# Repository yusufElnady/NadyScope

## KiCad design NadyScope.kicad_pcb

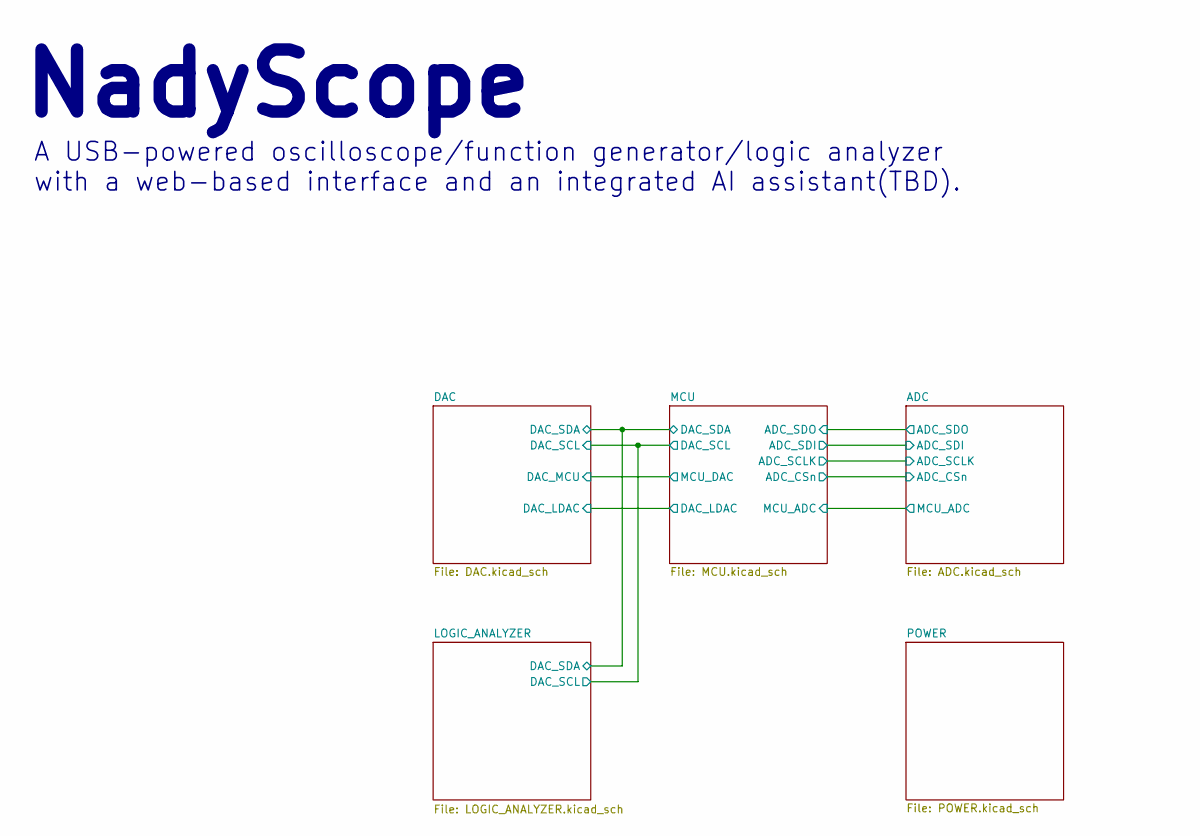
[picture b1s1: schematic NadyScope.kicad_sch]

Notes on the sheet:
A USB-powered oscilloscope/function generator/logic analyzer with a web-based interface and an integrated AI assistant(TBD).
NadyScope

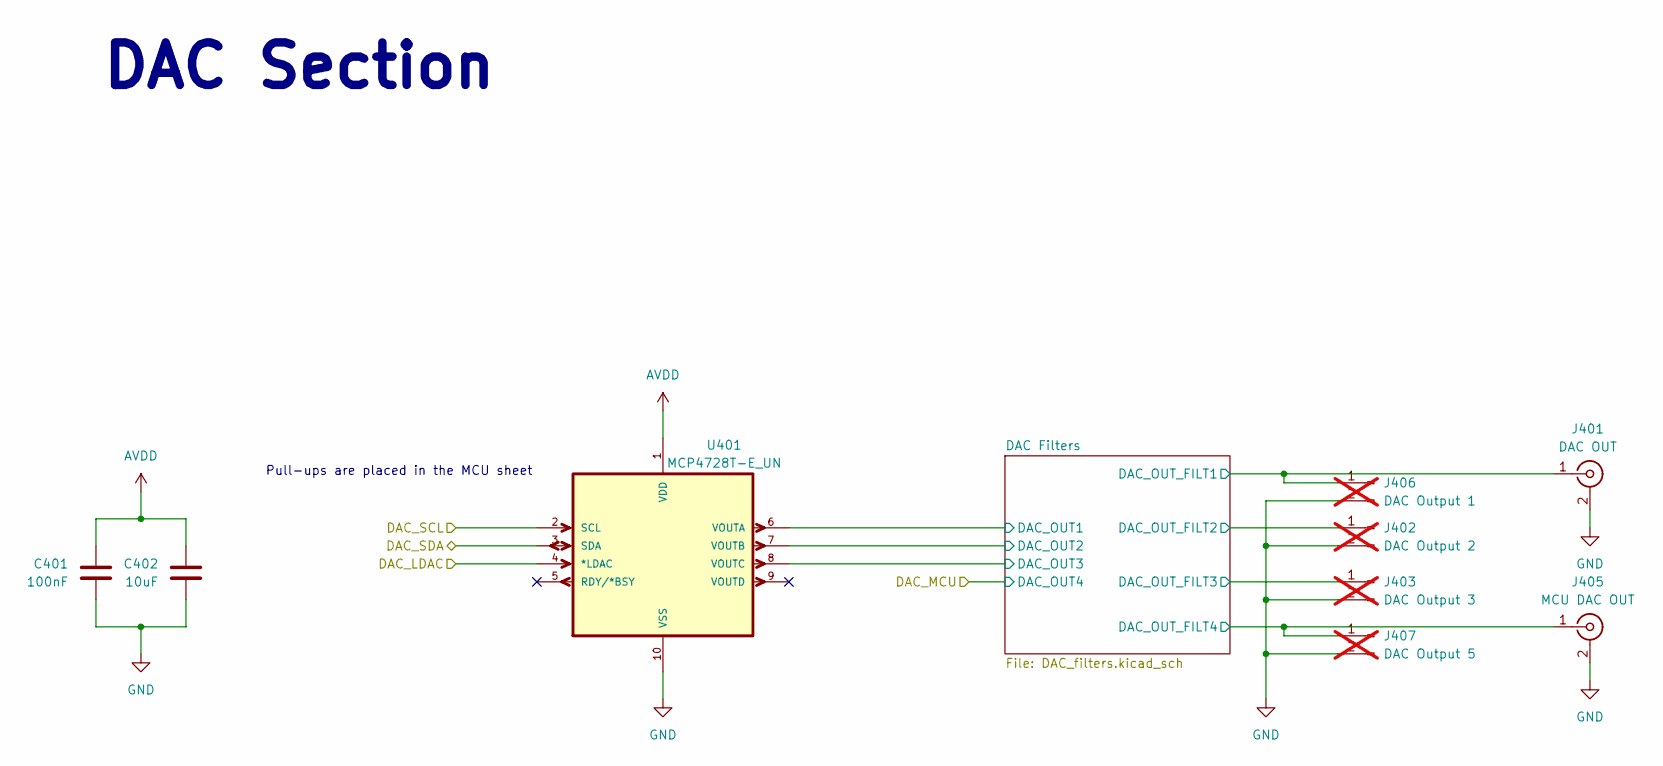
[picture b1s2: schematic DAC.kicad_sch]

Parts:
C401: 100nF; C_0603_1608Metric; MPN 0603B104M250CT
C402: 10uF; C_0603_1608Metric; MPN CL10A106MP8NNNC
J401: DAC OUT; CONN4_DOSIN-801_DOS; MPN DOSIN-801-0083
J402: DAC Output 2; PinHeader_1x02_P2.54mm_Vertical; not fitted
J403: DAC Output 3; PinHeader_1x02_P2.54mm_Vertical; not fitted
J405: MCU DAC OUT; CONN4_DOSIN-801_DOS; MPN DOSIN-801-0083
J406: DAC Output 1; PinHeader_1x02_P2.54mm_Vertical; not fitted
J407: DAC Output 5; PinHeader_1x02_P2.54mm_Vertical; not fitted
U401: MCP4728T-E_UN; SOP50P490X110-10N; MPN MCP4728T-E/UN

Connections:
/DAC/DAC Filters/DAC_OUT1: U401.6 (VOUTA); also elsewhere on the board
/DAC/DAC Filters/DAC_OUT2: U401.7 (VOUTB); also elsewhere on the board
/DAC/DAC Filters/DAC_OUT3: U401.8 (VOUTC); also elsewhere on the board
/DAC/DAC Filters/DAC_OUT_FILT1: J401.1 (In), J406.1; also elsewhere on the board
/DAC/DAC Filters/DAC_OUT_FILT2: J402.1; also elsewhere on the board
/DAC/DAC Filters/DAC_OUT_FILT3: J403.1; also elsewhere on the board
/DAC/DAC Filters/DAC_OUT_FILT4: J405.1 (In), J407.1; also elsewhere on the board
/DAC/DAC_LDAC: U401.4 (*LDAC); also elsewhere on the board
/DAC/DAC_SCL: U401.2 (SCL); also elsewhere on the board
/DAC/DAC_SDA: U401.3 (SDA); also elsewhere on the board
AVDD: C401.1, C402.1, U401.1 (VDD); also elsewhere on the board
GND: C401.2, C402.2, J401.2 (Ext), J402.2, J403.2, J405.2 (Ext), J406.2, J407.2, U401.10 (VSS); also elsewhere on the board

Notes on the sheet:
DAC Section
Pull-ups are placed in the MCU sheet

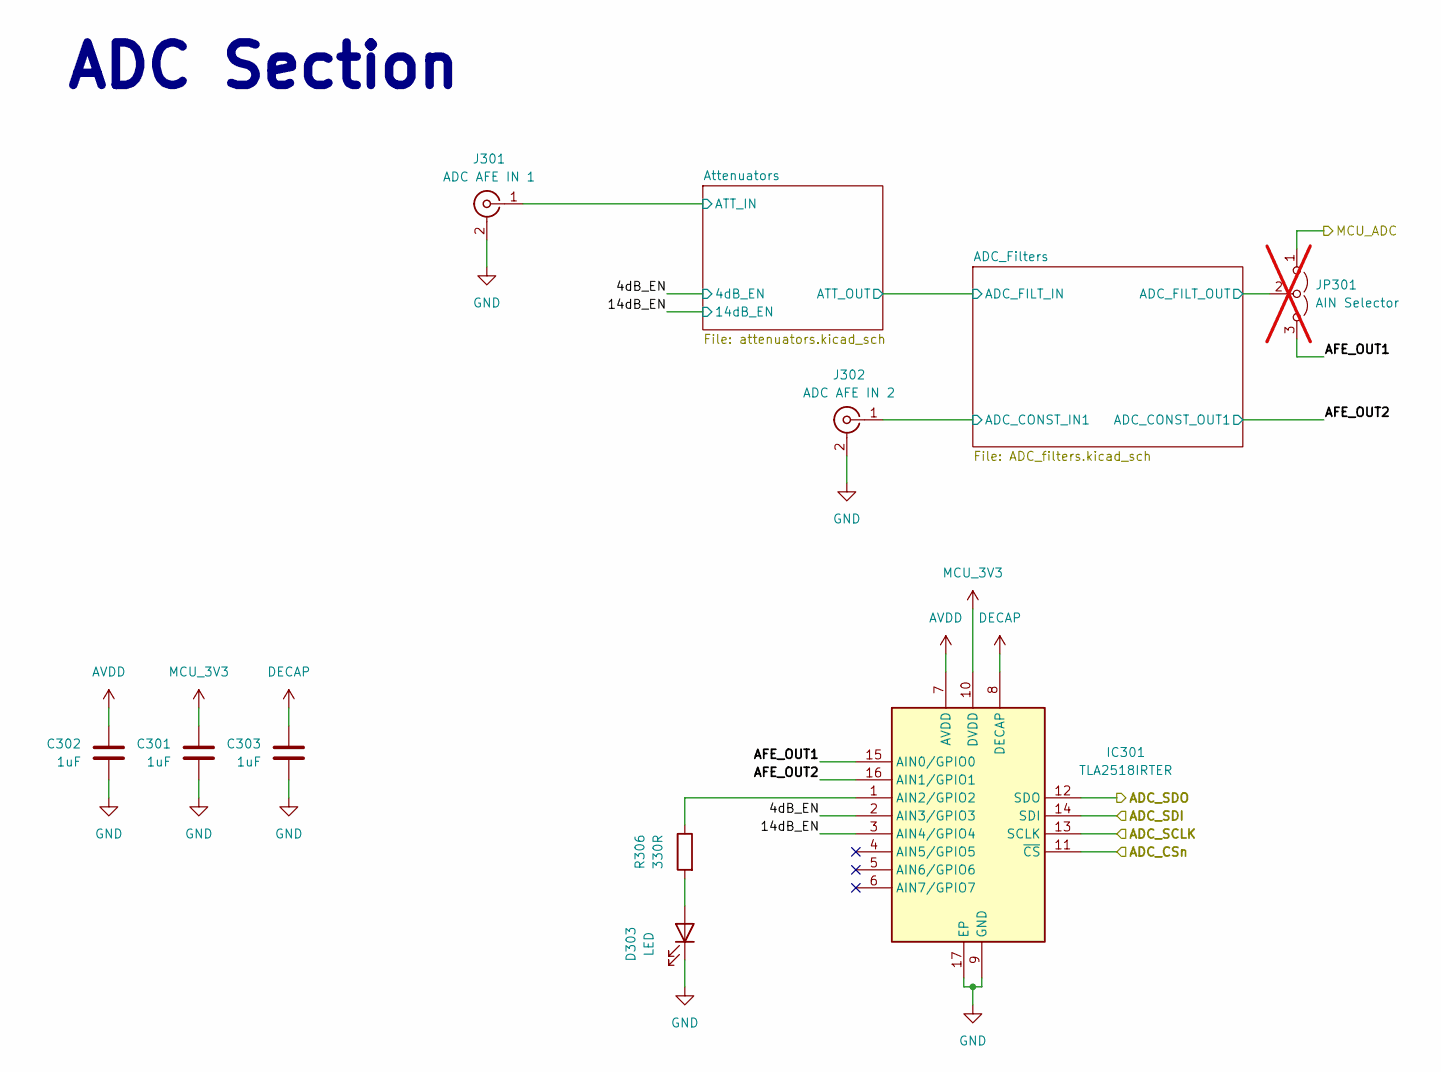
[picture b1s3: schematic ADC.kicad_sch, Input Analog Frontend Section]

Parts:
C301, C302, C303: 1uF; C_0603_1608Metric; MPN 0603X105K250CT
D303: LED; LED_0805_2012Metric
IC301: TLA2518IRTER; QFN50P300X300X80-17N-D; Manufacturer_Part_Number TLA2518IRTER; Mouser Part Number 595-TLA2518IRTER
J301: ADC AFE IN 1; CONN4_DOSIN-801_DOS; MPN DOSIN-801-0083
J302: ADC AFE IN 2; CONN4_DOSIN-801_DOS; MPN DOSIN-801-0083
JP301: AIN Selector; SolderJumper-3_P1.3mm_Open_Pad1.0x1.5mm; not fitted
R306: 330R; R_0603_1608Metric; MPN TD03G3300BT

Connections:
/ADC/4dB_EN: IC301.2 (AIN3/GPIO3); also elsewhere on the board
/ADC/14dB_EN: IC301.3 (AIN4/GPIO4); also elsewhere on the board
/ADC/ADC_CSn: IC301.11 (~CS); also elsewhere on the board
/ADC/ADC_Filters/ADC_FILT_OUT: JP301.2 (C); also elsewhere on the board
/ADC/ADC_SCLK: IC301.13 (SCLK); also elsewhere on the board
/ADC/ADC_SDI: IC301.14 (SDI); also elsewhere on the board
/ADC/ADC_SDO: IC301.12 (SDO); also elsewhere on the board
/ADC/AFE_OUT1: IC301.15 (AIN0/GPIO0), JP301.3 (B)
/ADC/AFE_OUT2: IC301.16 (AIN1/GPIO1); also elsewhere on the board
/ADC/MCU_ADC: JP301.1 (A); also elsewhere on the board
AVDD: C302.1, IC301.7 (AVDD); also elsewhere on the board
DECAP: C303.1, IC301.8 (DECAP)
GND: C301.2, C302.2, C303.2, D303.1 (K), IC301.9 (GND), IC301.17 (EP), J301.2 (Ext), J302.2 (Ext); also elsewhere on the board
MCU_3V3: C301.1, IC301.10 (DVDD); also elsewhere on the board
unnamed: D303.2 (A), R306.2
unnamed: IC301.1 (AIN2/GPIO2), R306.1

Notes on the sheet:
ADC Section

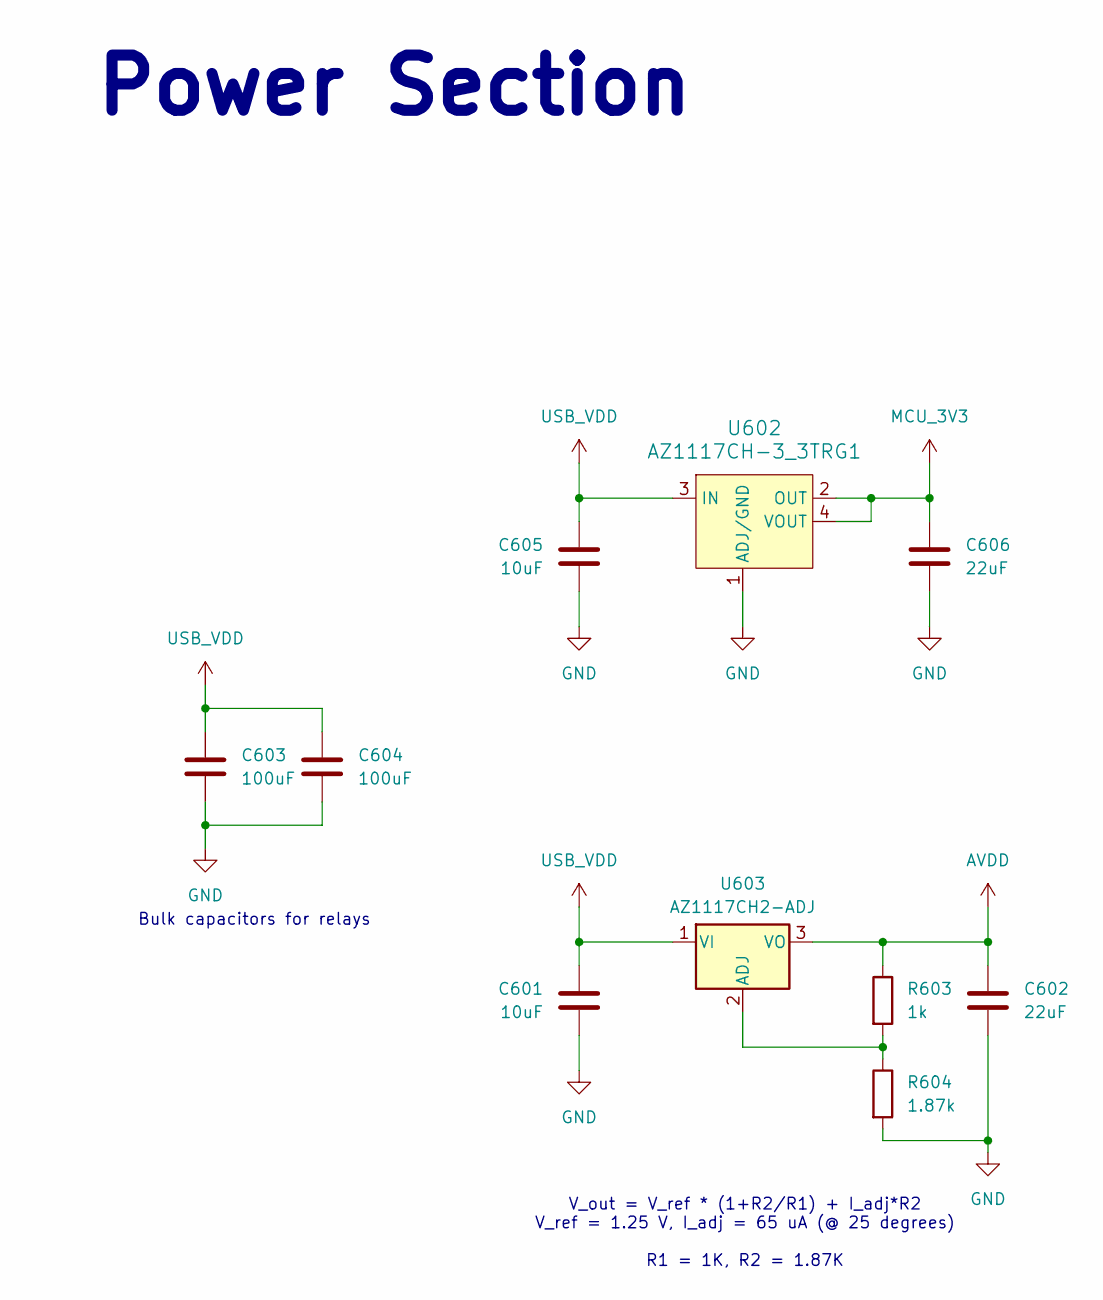
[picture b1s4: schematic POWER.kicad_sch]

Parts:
C601, C605: 10uF; C_0805_2012Metric; MPN CL21A106KOQNNNE
C602, C606: 22uF; C_0805_2012Metric; MPN CL21X226MRQNNNE
C603, C604: 100uF; C_1206_3216Metric; MPN TCC1206X7R103M501DTS
R603: 1k; R_0603_1608Metric; MPN RT0603BRD071KL
R604: 1.87k; R_0603_1608Metric; MPN PTFR0603B1K87N9
U602: AZ1117CH-3_3TRG1; SOT-223; MPN AZ1117CH-3.3TRG1; Digi-Key_PN AZ1117CH-3.3TRG1DICT-ND
U603: AZ1117CH2-ADJ; SOT-223-3_TabPin2; MPN AZ1117CH2-ADJ

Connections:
AVDD: C602.1, R603.1, U603.3 (VO); also elsewhere on the board
GND: C601.2, C602.2, C603.2, C604.2, C605.2, C606.2, R604.2, U602.1 (ADJ/GND); also elsewhere on the board
MCU_3V3: C606.1, U602.2 (OUT), U602.4 (VOUT); also elsewhere on the board
unnamed: R603.2, R604.1, U603.2 (ADJ)
USB_VDD: C601.1, C603.1, C604.1, C605.1, U602.3 (IN), U603.1 (VI); also elsewhere on the board

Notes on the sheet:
Bulk capacitors for relays
V_out = V_ref * (1+R2/R1) + I_adj*R2 V_ref = 1.25 V, I_adj = 65 uA (@ 25 degrees) R1 = 1K, R2 = 1.87K
Power Section

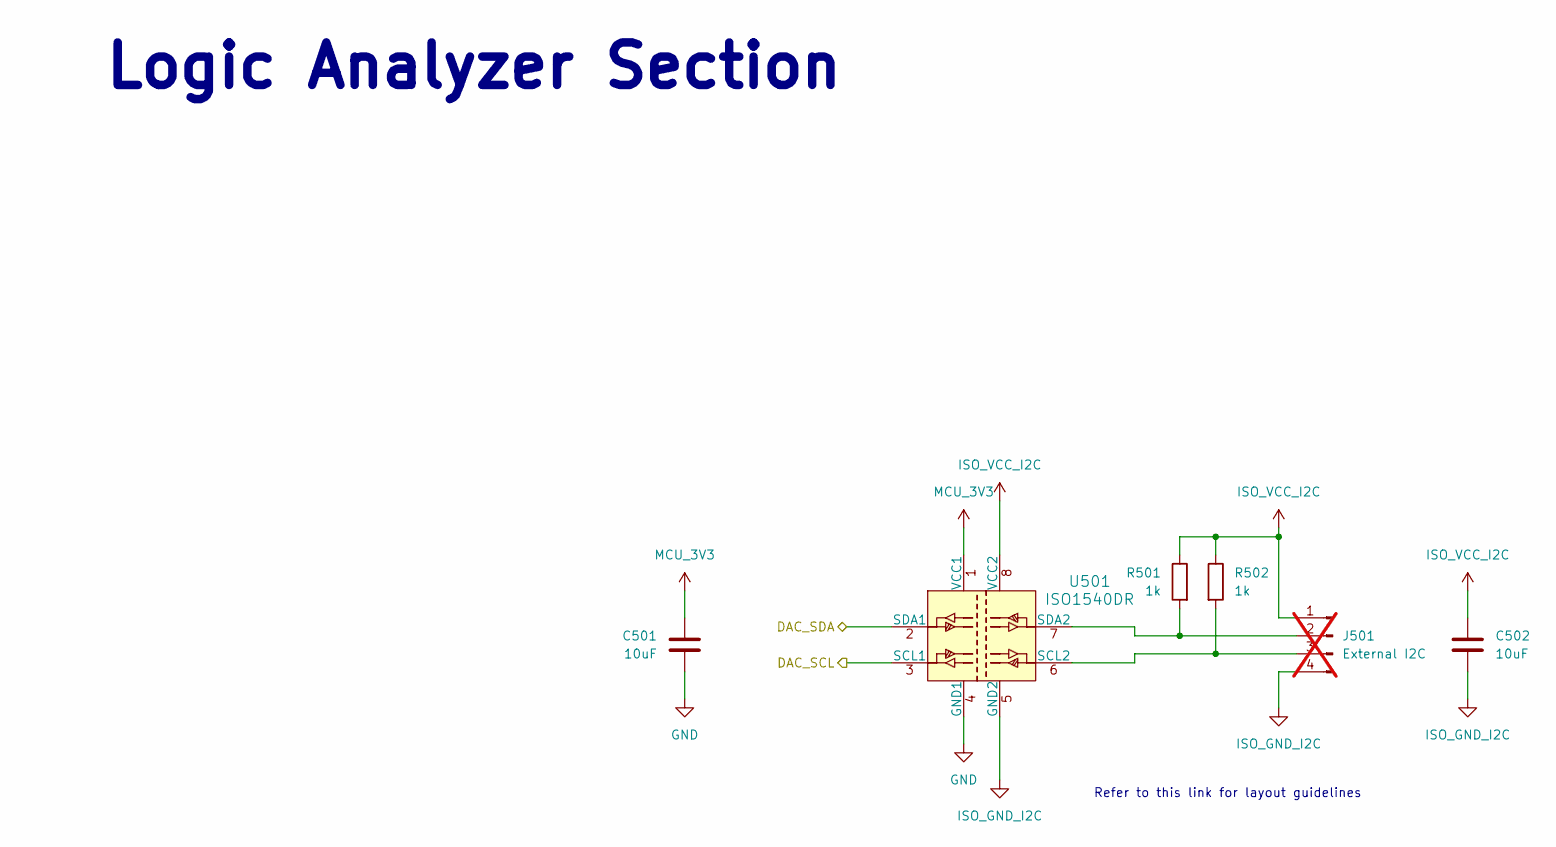
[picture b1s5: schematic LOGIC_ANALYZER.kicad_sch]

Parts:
C501, C502: 10uF; C_0603_1608Metric; MPN CL10A106MP8NNNC
J501: External I2C; PinHeader_1x04_P2.54mm_Vertical; not fitted
R501, R502: 1k; R_0603_1608Metric; MPN RT0603BRD071KL
U501: ISO1540DR; SOIC-8_W3.9mm; MPN ISO1540DR; Digi-Key_PN 296-34871-1-ND

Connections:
/DAC/DAC_SCL: U501.3 (SCL1); also elsewhere on the board
/DAC/DAC_SDA: U501.2 (SDA1); also elsewhere on the board
GND: C501.2, U501.4 (GND1); also elsewhere on the board
ISO_GND_I2C: C502.2, J501.4, U501.5 (GND2)
ISO_VCC_I2C: C502.1, J501.1, R501.1, R502.1, U501.8 (VCC2)
MCU_3V3: C501.1, U501.1 (VCC1); also elsewhere on the board
unnamed: J501.2, R501.2, U501.7 (SDA2)
unnamed: J501.3, R502.2, U501.6 (SCL2)

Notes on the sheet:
Logic Analyzer Section
Refer to this link for layout guidelines

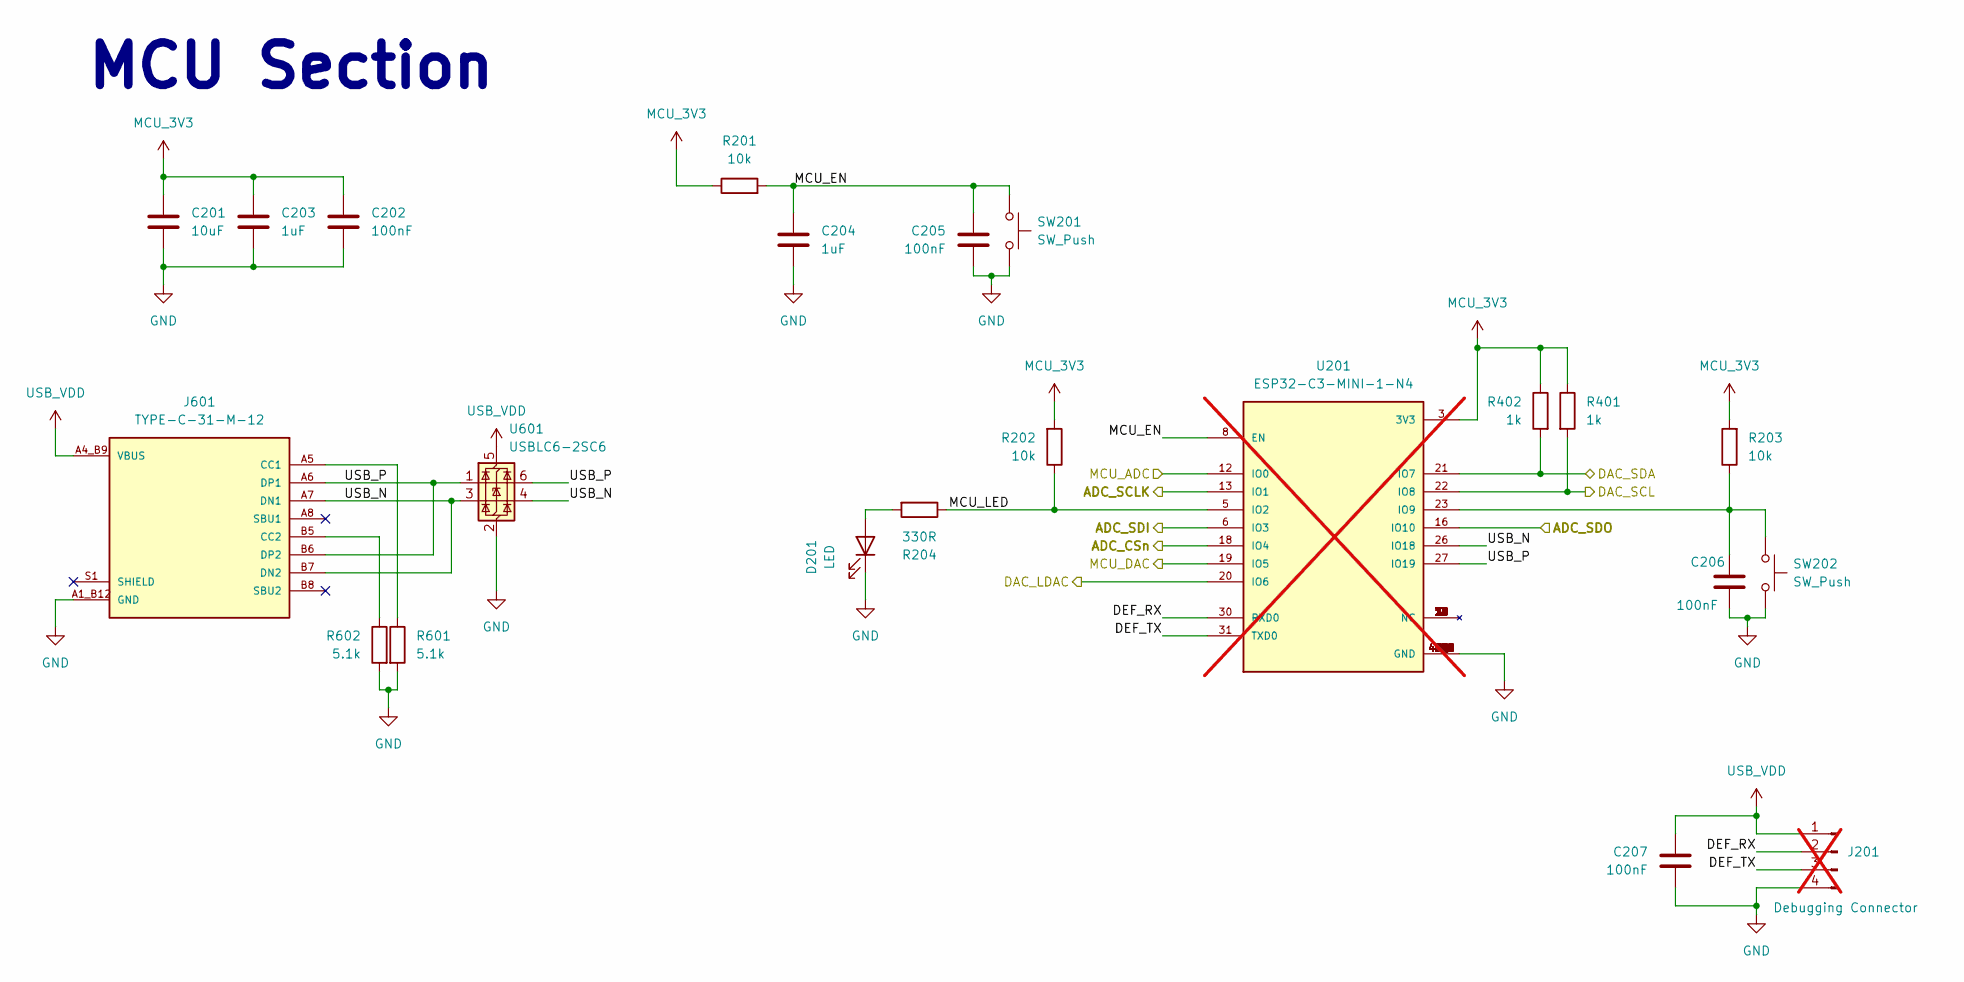
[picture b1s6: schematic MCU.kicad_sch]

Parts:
C201: 10uF; C_0603_1608Metric; MPN CL10A106MP8NNNC
C202, C205, C206, C207: 100nF; C_0603_1608Metric; MPN 0603B104M250CT
C203, C204: 1uF; C_0603_1608Metric; MPN 0603X105K250CT
D201: LED; LED_0805_2012Metric
J201: Debugging Connector; PinHeader_1x04_P2.54mm_Vertical; not fitted
J601: TYPE-C-31-M-12; HRO_TYPE-C-31-M-12; PARTREV 2020.12.08
R201, R202, R203: 10k; R_0603_1608Metric; MPN TD03G1002BT
R204: 330R; R_0603_1608Metric; MPN TD03G3300BT
R401, R402: 1k; R_0603_1608Metric; MPN RT0603BRD071KL
R601, R602: 5.1k; R_0603_1608Metric; MPN RT0603BRD075K1L
SW201, SW202: SW_Push; SW_Push_SPST_NO_Alps_SKRK
U201: ESP32-C3-MINI-1-N4; XCVR_ESP32-C3-MINI-1-N4; PARTREV v1.0; not fitted
U601: USBLC6-2SC6; SOT-23-6; MPN USBLC6-2SC6

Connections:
/ADC/ADC_CSn: U201.18 (IO4); also elsewhere on the board
/ADC/ADC_SCLK: U201.13 (IO1); also elsewhere on the board
/ADC/ADC_SDI: U201.6 (IO3); also elsewhere on the board
/ADC/ADC_SDO: U201.16 (IO10); also elsewhere on the board
/ADC/MCU_ADC: U201.12 (IO0); also elsewhere on the board
/DAC/DAC_LDAC: U201.20 (IO6); also elsewhere on the board
/DAC/DAC_MCU: U201.19 (IO5); also elsewhere on the board
/DAC/DAC_SCL: R401.2, U201.22 (IO8); also elsewhere on the board
/DAC/DAC_SDA: R402.2, U201.21 (IO7); also elsewhere on the board
/MCU/DEF_RX: J201.2, U201.30 (RXD0)
/MCU/DEF_TX: J201.3, U201.31 (TXD0)
/MCU/MCU_EN: C204.1, C205.1, R201.2, SW201.1, U201.8 (EN)
/MCU/MCU_LED: R202.1, R204.1, U201.5 (IO2)
/MCU/USB_N: J601.A7 (DN1), J601.B7 (DN2), U201.26 (IO18), U601.3 (I/O2), U601.4 (I/O2)
/MCU/USB_P: J601.A6 (DP1), J601.B6 (DP2), U201.27 (IO19), U601.1 (I/O1), U601.6 (I/O1)
GND: C201.2, C202.2, C203.2, C204.2, C205.2, C206.2, C207.2, D201.1 (K), J201.4, J601.A1_B12 (GND), J601.B1_A12 (GND), R601.2, R602.2, SW201.2, SW202.2, U201.1 (GND), U201.2 (GND), U201.11 (GND), U201.14 (GND), U201.36 (GND), U201.37 (GND), U201.38 (GND), U201.39 (GND), U201.40 (GND), U201.41 (GND), U201.42 (GND), U201.43 (GND), U201.44 (GND), U201.45 (GND), U201.46 (GND), U201.47 (GND), U201.48 (GND), U201.49_1 (GND), U201.49_2 (GND), U201.49_3 (GND), U201.49_4 (GND), U201.49_5 (GND), U201.49_6 (GND), U201.49_7 (GND), U201.49_8 (GND), U201.49_9 (GND), U201.50 (GND), U201.51 (GND), U201.52 (GND), U201.53 (GND), U601.2 (GND); also elsewhere on the board
MCU_3V3: C201.1, C202.1, C203.1, R201.1, R202.2, R203.2, R401.1, R402.1, U201.3 (3V3); also elsewhere on the board
unnamed: D201.2 (A), R204.2
unnamed: J601.A5 (CC1), R601.1
unnamed: J601.B5 (CC2), R602.1
unnamed: C206.1, R203.1, SW202.1, U201.23 (IO9)
USB_VDD: C207.1, J201.1, J601.A4_B9 (VBUS), J601.B4_A9 (VBUS), U601.5 (VBUS); also elsewhere on the board

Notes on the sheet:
MCU Section

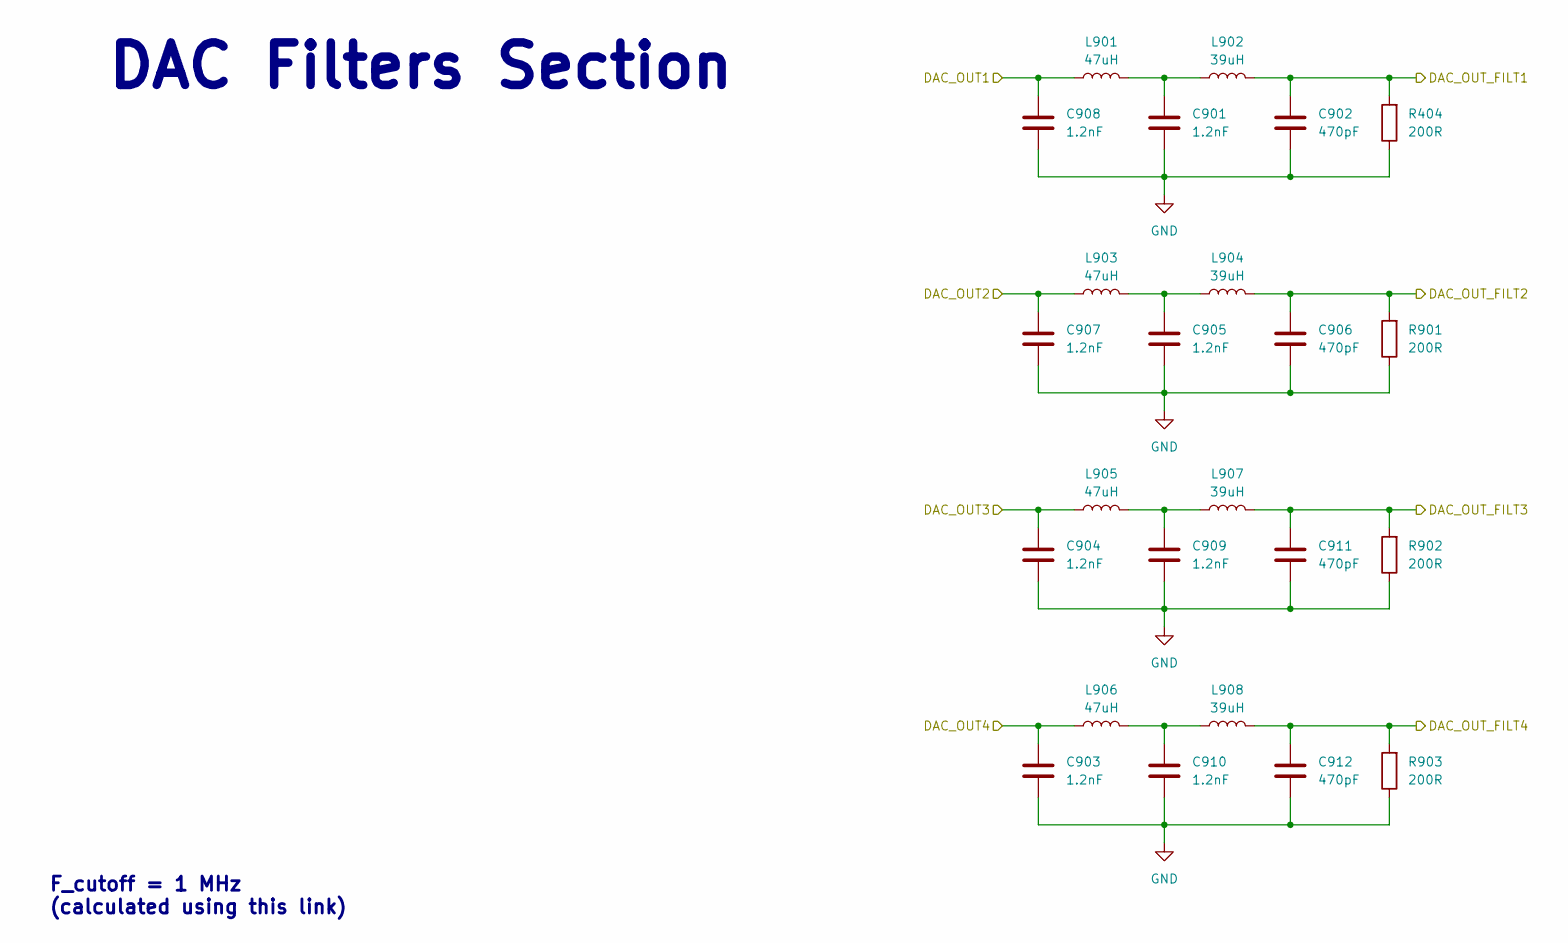
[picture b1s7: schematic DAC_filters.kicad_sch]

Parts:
C901, C903, C904, C905, C907, C908, C909, C910: 1.2nF; C_0603_1608Metric; MPN CGA0603X7R122K500JT
C902, C906, C911, C912: 470pF; C_0603_1608Metric; MPN FCC0603B471K500CT
L901, L903, L905, L906: 47uH; L_0603_1608Metric; MPN WI0603LD470KST-HF
L902, L904, L907, L908: 39uH; L_0805_2012Metric; MPN MLI2012F-390KT
R404, R901, R902, R903: 200R; R_0603_1608Metric; MPN PTFR0603B200RP9

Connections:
/DAC/DAC Filters/DAC_OUT1: C908.1, L901.1; also elsewhere on the board
/DAC/DAC Filters/DAC_OUT2: C907.1, L903.1; also elsewhere on the board
/DAC/DAC Filters/DAC_OUT3: C904.1, L905.1; also elsewhere on the board
/DAC/DAC Filters/DAC_OUT_FILT1: C902.1, L902.2, R404.2; also elsewhere on the board
/DAC/DAC Filters/DAC_OUT_FILT2: C906.1, L904.2, R901.2; also elsewhere on the board
/DAC/DAC Filters/DAC_OUT_FILT3: C911.1, L907.2, R902.2; also elsewhere on the board
/DAC/DAC Filters/DAC_OUT_FILT4: C912.1, L908.2, R903.2; also elsewhere on the board
/DAC/DAC_MCU: C903.1, L906.1; also elsewhere on the board
GND: C901.2, C902.2, C903.2, C904.2, C905.2, C906.2, C907.2, C908.2, C909.2, C910.2, C911.2, C912.2, R404.1, R901.1, R902.1, R903.1; also elsewhere on the board
unnamed: C901.1, L901.2, L902.1
unnamed: C905.1, L903.2, L904.1
unnamed: C909.1, L905.2, L907.1
unnamed: C910.1, L906.2, L908.1

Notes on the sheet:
F_cutoff = 1 MHz (calculated using this link)
DAC Filters Section

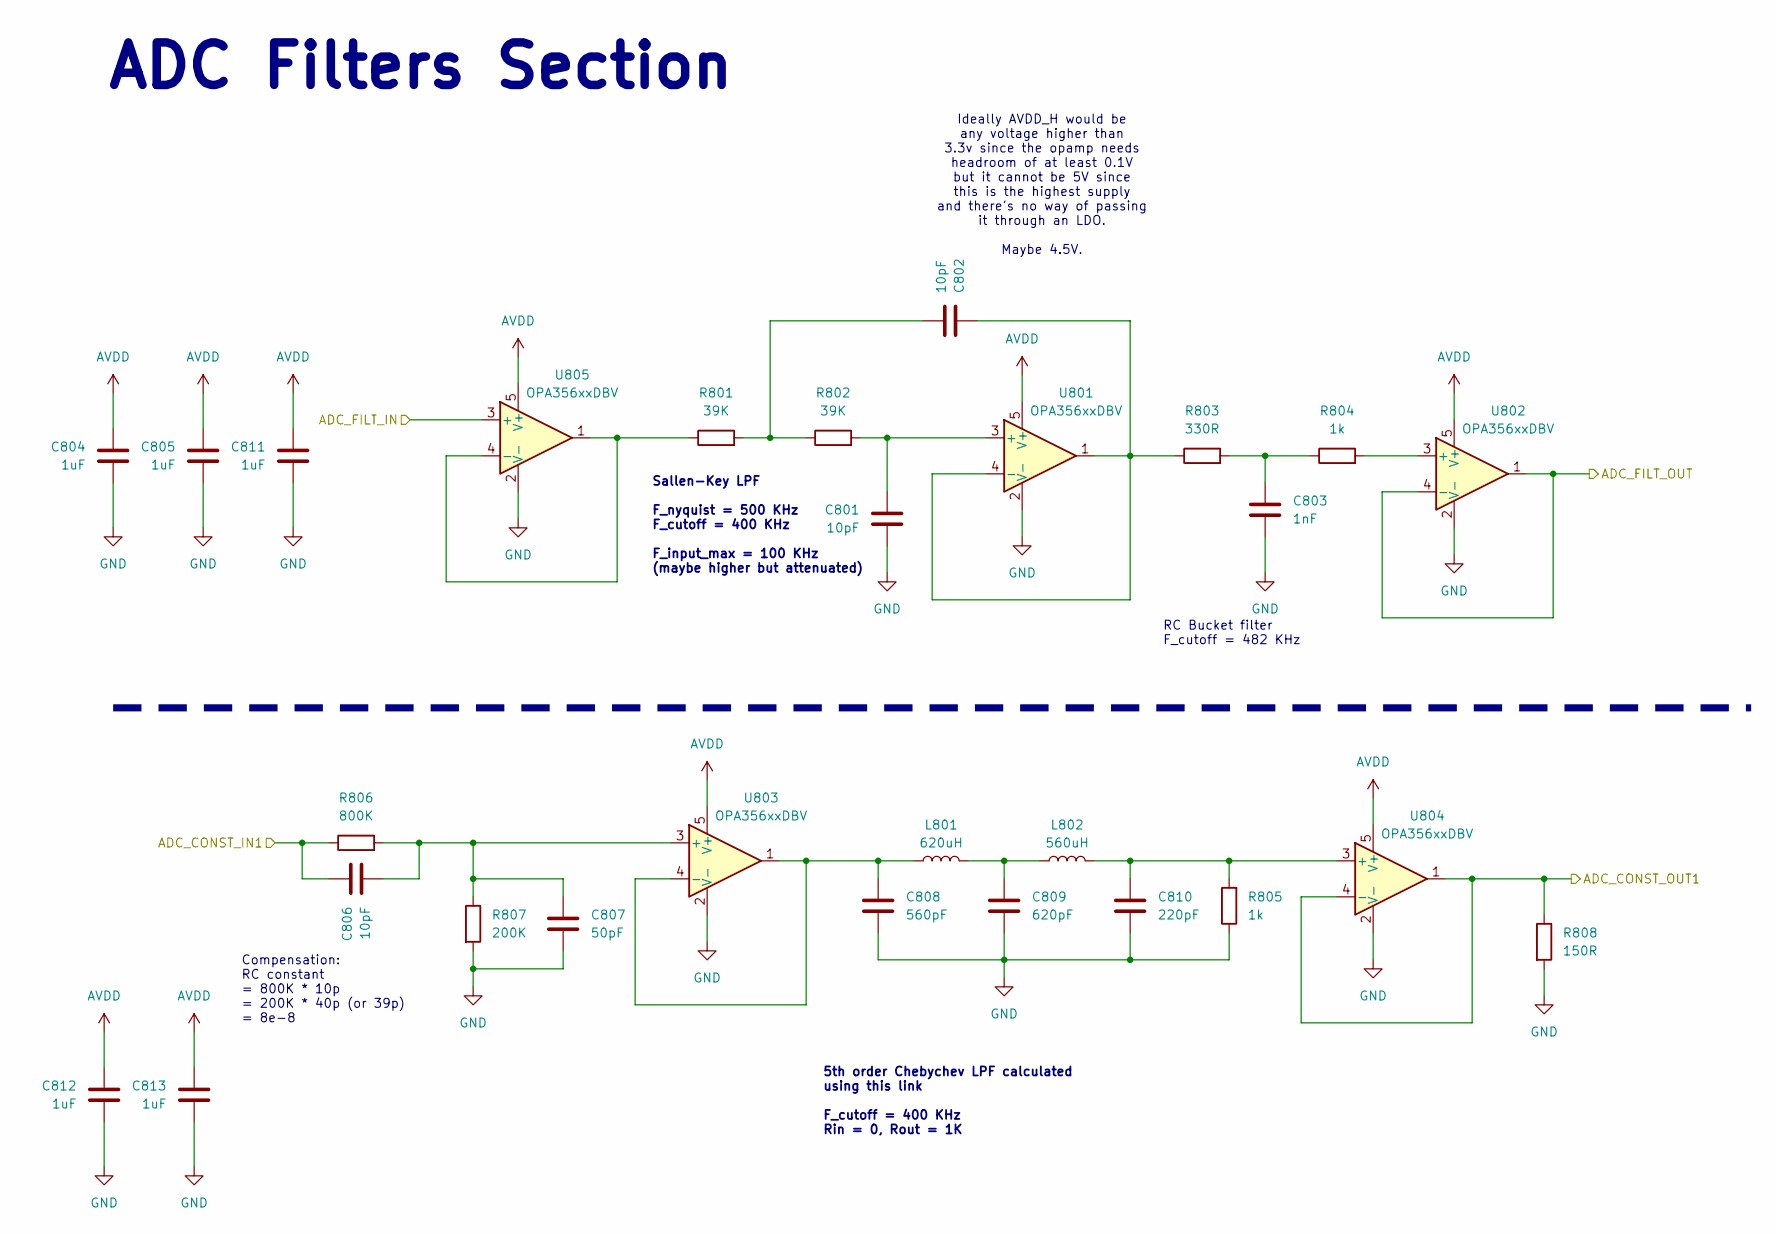
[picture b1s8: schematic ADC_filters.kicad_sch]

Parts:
C801, C802, C806: 10pF; C_0603_1608Metric; MPN FCC0603N100J500CT
C803: 1nF; C_0603_1608Metric; MPN CL10B102KB8NNNC
C804, C805, C811, C812, C813: 1uF; C_0603_1608Metric; MPN 0603X105K250CT
C807: 50pF; C_0603_1608Metric; MPN CC0603JRNPO9BN510
C808: 560pF; C_0603_1608Metric; MPN TCC0603X7R561K500CT
C809: 620pF; C_0603_1608Metric; MPN CC0603JRNPO9BN621
C810: 220pF; C_0603_1608Metric; MPN CS1608X7R221K500NRB
L801: 620uH; L_1210_3225Metric; MPN MWI1210IF621KST-HF
L802: 560uH; L_1210_3225Metric; MPN AHW3225F-561KTF
R801, R802: 39K; R_0603_1608Metric; MPN RT0603BRD0739KL
R803: 330R; R_0603_1608Metric; MPN TD03G3300BT
R804, R805: 1k; R_0603_1608Metric; MPN RT0603BRD071KL
R806: 800K; R_0603_1608Metric; MPN HoARG0603-1/10W-820KR-0.1%-TCR25
R807: 200K; R_0603_1608Metric; MPN ERA3AEB204V
R808: 150R; R_0603_1608Metric; MPN RT0603BRD07150RL
U801, U802, U803, U804, U805: OPA356xxDBV; SOT-23-5

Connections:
/ADC/ADC_Filters/ADC_CONST_IN1: C806.1, R806.1; also elsewhere on the board
/ADC/ADC_Filters/ADC_FILT_IN: U805.3 (+); also elsewhere on the board
/ADC/ADC_Filters/ADC_FILT_OUT: U802.1, U802.4 (-); also elsewhere on the board
/ADC/AFE_OUT2: R808.1, U804.1, U804.4 (-); also elsewhere on the board
AVDD: C804.1, C805.1, C811.1, C812.1, C813.1, U801.5 (V+), U802.5 (V+), U803.5 (V+), U804.5 (V+), U805.5 (V+); also elsewhere on the board
GND: C801.2, C803.2, C804.2, C805.2, C807.2, C808.2, C809.2, C810.2, C811.2, C812.2, C813.2, R805.1, R807.2, R808.2, U801.2 (V-), U802.2 (V-), U803.2 (V-), U804.2 (V-), U805.2 (V-); also elsewhere on the board
unnamed: C802.2, R801.2, R802.1
unnamed: C803.1, R803.2, R804.1
unnamed: C809.1, L801.2, L802.1
unnamed: C801.1, R802.2, U801.3 (+)
unnamed: C802.1, R803.1, U801.1, U801.4 (-)
unnamed: R804.2, U802.3 (+)
unnamed: C806.2, C807.1, R806.2, R807.1, U803.3 (+)
unnamed: C808.1, L801.1, U803.1, U803.4 (-)
unnamed: C810.1, L802.2, R805.2, U804.3 (+)
unnamed: R801.1, U805.1, U805.4 (-)

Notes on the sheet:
Compensation: RC constant = 800K * 10p = 200K * 40p (or 39p) = 8e-8
Ideally AVDD_H would be any voltage higher than 3.3v since the opamp needs headroom of at least 0.1V but it cannot be 5V since this is the highest supply and there's no way of passing it through an LDO. Maybe 4.5V.
ADC Filters Section
RC Bucket filter F_cutoff = 482 KHz
Sallen-Key LPF F_nyquist = 500 KHz F_cutoff = 400 KHz F_input_max = 100 KHz (maybe higher but attenuated)
5th order Chebychev LPF calculated using this link F_cutoff = 400 KHz Rin = 0, Rout = 1K

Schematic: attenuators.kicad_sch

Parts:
C701, C703: 10pF; C_0603_1608Metric; MPN FCC0603N100J500CT
C702: 50pF; C_0603_1608Metric; MPN CC0603JRNPO9BN510
C704: 17pF; C_0603_1608Metric; MPN 0603N180J500CT
D301, D302: 1N4148W; D_SOD-123; MPN 1N4148W
K301, K302: FTR-B3GA4.5Z-B10; FTRB3GA45ZB10; Manufacturer_Part_Number FTR-B3GA4.5Z-B10
Q301, Q302: BC817; SOT-23; MPN BC817
R301, R309: 500R; R_0603_1608Metric; MPN RT0603BRD07500RL
R302: 800K; R_0603_1608Metric; MPN HoARG0603-1/10W-820KR-0.1%-TCR25
R303: 200K; R_0603_1608Metric; MPN ERA3AEB204V
R304: 370K; R_0603_1608Metric; MPN ARG03BTC3653
R305: 630K; R_0603_1608Metric; MPN ARG03BTC6493

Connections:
/ADC/4dB_EN: R301.1; also elsewhere on the board
/ADC/14dB_EN: R309.1; also elsewhere on the board
/ADC/ADC_Filters/ADC_FILT_IN: K302.6 (COM2); also elsewhere on the board
/ADC/Attenuators/4dB_IN: C704.1, K302.2 (NC1), R304.1
/ADC/Attenuators/4dB_OUT: C703.2, C704.2, K302.7 (NC2), R304.2, R305.1
/ADC/Attenuators/4dB_SW: D302.2 (A), K302.8 (COIL-), Q302.3 (C)
/ADC/Attenuators/14dB_IN: C701.1, K301.2 (NC1), R302.1
/ADC/Attenuators/14dB_OUT: C701.2, C702.1, K301.7 (NC2), R302.2, R303.1
/ADC/Attenuators/14dB_SW: D301.2 (A), K301.8 (COIL-), Q301.3 (C)
/ADC/Attenuators/ATT_IN: K301.3 (COM1); also elsewhere on the board
/ADC/Attenuators/SKIP_4dB: K302.4 (NO1), K302.5 (NO2)
/ADC/Attenuators/SKIP_14dB: K301.4 (NO1), K301.5 (NO2)
/ADC/Attenuators/mid_attenuators: K301.6 (COM2), K302.3 (COM1)
GND: C702.2, C703.1, Q301.2 (E), Q302.2 (E), R303.2, R305.2; also elsewhere on the board
unnamed: Q301.1 (B), R309.2
unnamed: Q302.1 (B), R301.2
USB_VDD: D301.1 (K), D302.1 (K), K301.1 (COIL+), K302.1 (COIL+); also elsewhere on the board

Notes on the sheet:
With 4 voltage settings, the default is the highest setting and the MCU would switch down if the voltage is detected to fit within tighter ones.
Compensation: RC constant = 370K * 17p = 630K * 10p = 6.3e-8
Input Attenuators Section
Compensation: RC constant = 800K * 10p = 200K * 40p (or 39p) = 8e-8

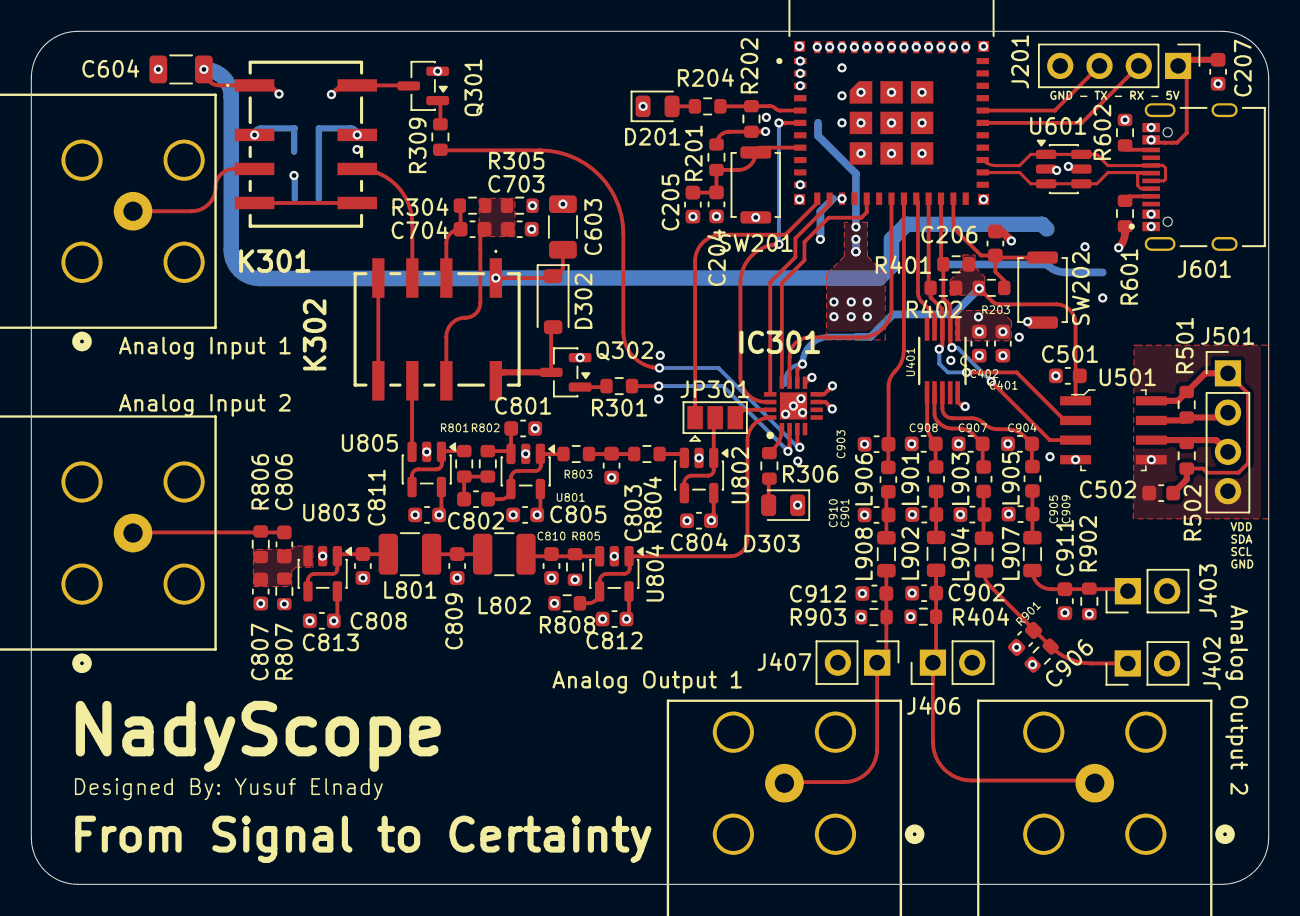
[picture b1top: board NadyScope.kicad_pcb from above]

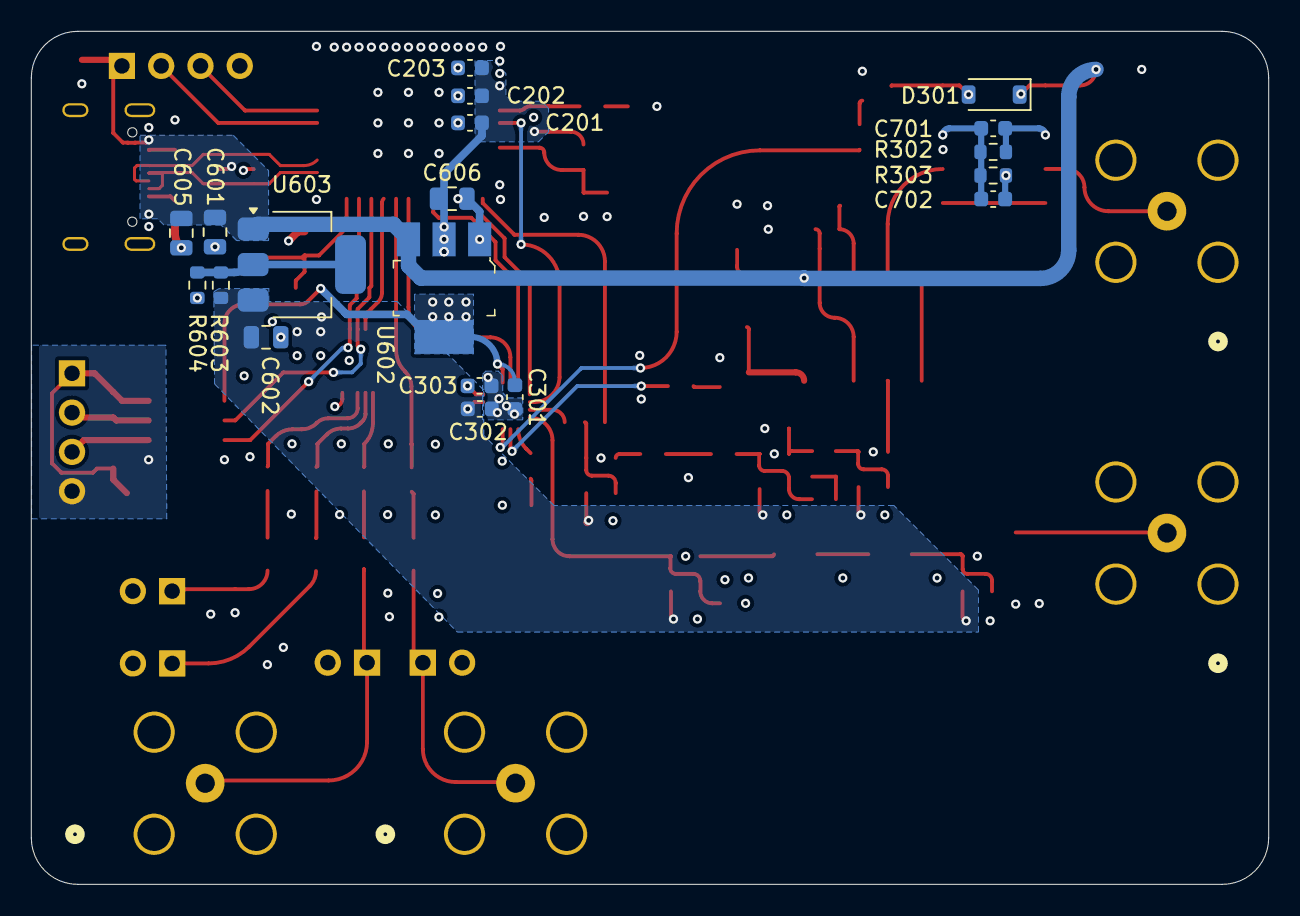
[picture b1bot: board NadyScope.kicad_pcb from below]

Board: 4 copper layers, 80.0 x 55.2 mm, 124 parts (19 on the bottom side), 71 nets.

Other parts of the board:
Analog Input 1: ADC AFE IN 1; CONN4_DOSIN-801_DOS
Analog Input 2: ADC AFE IN 2; CONN4_DOSIN-801_DOS
Analog Output 1: MCU DAC OUT; CONN4_DOSIN-801_DOS
Analog Output 2: DAC OUT; CONN4_DOSIN-801_DOS

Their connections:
/ADC/ADC_Filters/ADC_CONST_IN1: Analog Input 2.1 (In); also elsewhere on the board
/ADC/Attenuators/ATT_IN: Analog Input 1.1 (In); also elsewhere on the board
/DAC/DAC Filters/DAC_OUT_FILT1: Analog Output 2.1 (In); also elsewhere on the board
/DAC/DAC Filters/DAC_OUT_FILT4: Analog Output 1.1 (In); also elsewhere on the board
GND: Analog Input 1.2 (Ext), Analog Input 2.2 (Ext), Analog Output 1.2 (Ext), Analog Output 2.2 (Ext); also elsewhere on the board
